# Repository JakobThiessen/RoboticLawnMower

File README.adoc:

= RoboticLawnMower
:TOC:

== Projektbeschreibung
Rasenmähroboter in Eigenbau

== Konzept

image::docs/Konzept_1.drawio.svg[static, 600]

== Projektübersicht

== Hardware
image::Hardware/KiCad/RoboticLawnMower/3D_TOP.png[static, 600]

image::Hardware/KiCad/RoboticLawnMower/3D_BOT.png[static, 600]

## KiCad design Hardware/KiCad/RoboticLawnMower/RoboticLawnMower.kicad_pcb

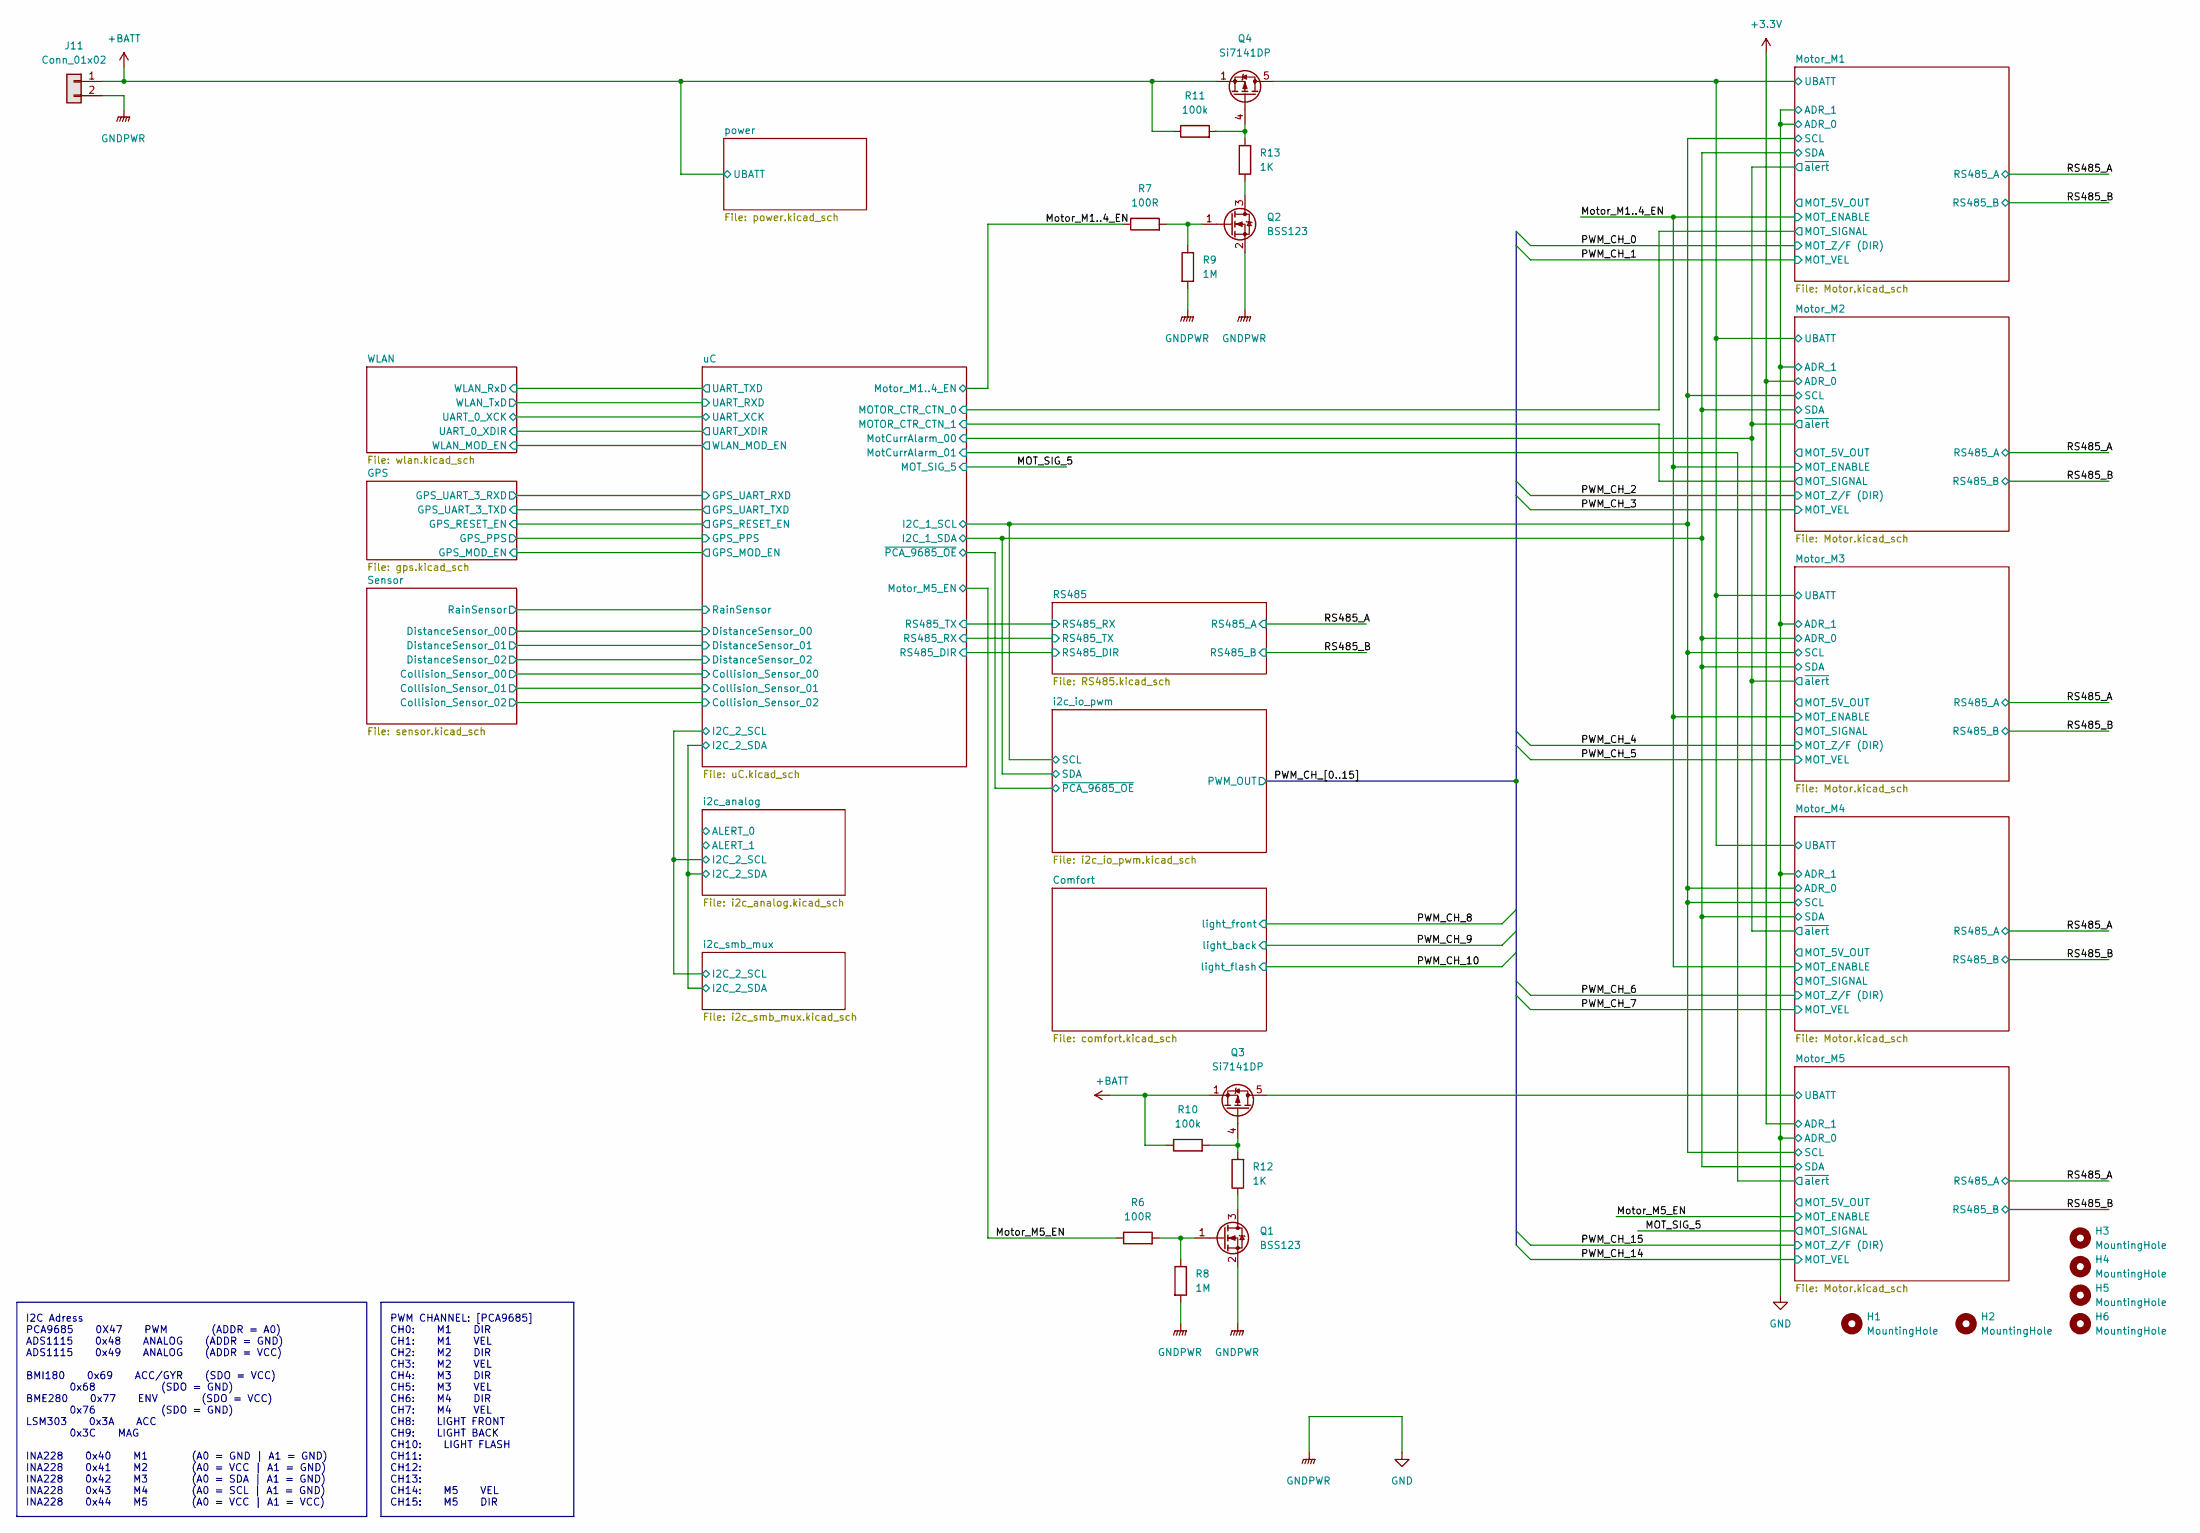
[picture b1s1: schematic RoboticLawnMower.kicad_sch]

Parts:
H1, H2, H3, H4, H5, H6: MountingHole; MountingHole_3.2mm_M3
J11: Conn_01x02; PhoenixContact_MCV_1,5_2-GF-3.81_1x02_P3.81mm_Vertical_Thre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
Q1, Q2: BSS123; SOT-23
Q3, Q4: Si7141DP; PowerPAK_SO-8_Single
R6, R7: 100R; R_0603_1608Metric
R8, R9: 1M; R_0603_1608Metric
R10, R11: 100k; R_0603_1608Metric
R12, R13: 1K; R_0603_1608Metric

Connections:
+BATT: J11.1, Q3.1 (S), Q3.2 (S), Q3.3 (S), Q4.1 (S), Q4.2 (S), Q4.3 (S), R10.1, R11.1; also elsewhere on the board
/Motor_M1..4_EN: R7.1; also elsewhere on the board
/Motor_M1/UBATT: Q4.5 (D); also elsewhere on the board
/Motor_M5/UBATT: Q3.5 (D); also elsewhere on the board
/Motor_M5_EN: R6.1; also elsewhere on the board
GND: J11.2, Q1.2 (S), Q2.2 (S), R8.2, R9.2; also elsewhere on the board
unnamed: Q1.3 (D), R12.1
unnamed: Q1.1 (G), R6.2, R8.1
unnamed: Q2.3 (D), R13.1
unnamed: Q2.1 (G), R7.2, R9.1
unnamed: Q3.4 (G), R10.2, R12.2
unnamed: Q4.4 (G), R11.2, R13.2

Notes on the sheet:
PWM CHANNEL: [PCA9685] CH0: M1 DIR CH1: M1 VEL CH2: M2 DIR CH3: M2 VEL CH4: M3 DIR CH5: M3 VEL CH6: M4 DIR CH7: M4 VEL CH8: LIGHT FRONT CH9: LIGHT BACK CH10: LIGHT FLASH CH11: CH12: CH13: CH14: M5 VEL CH15: M5 DIR
I2C Adress PCA9685 0X47 PWM (ADDR = A0) ADS1115 0x48 ANALOG (ADDR = GND) ADS1115 0x49 ANALOG (ADDR = VCC) BMI180 0x69 ACC/GYR (SDO = VCC) 0x68 (SDO = GND) BME280 0x77 ENV (SDO = VCC) 0x76 (SDO = GND) LSM303 0x3A ACC 0x3C MAG INA228 0x40 M1 (A0 = GND | A1 = GND) INA228 0x41 M2 (A0 = VCC | A1 = GND) 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

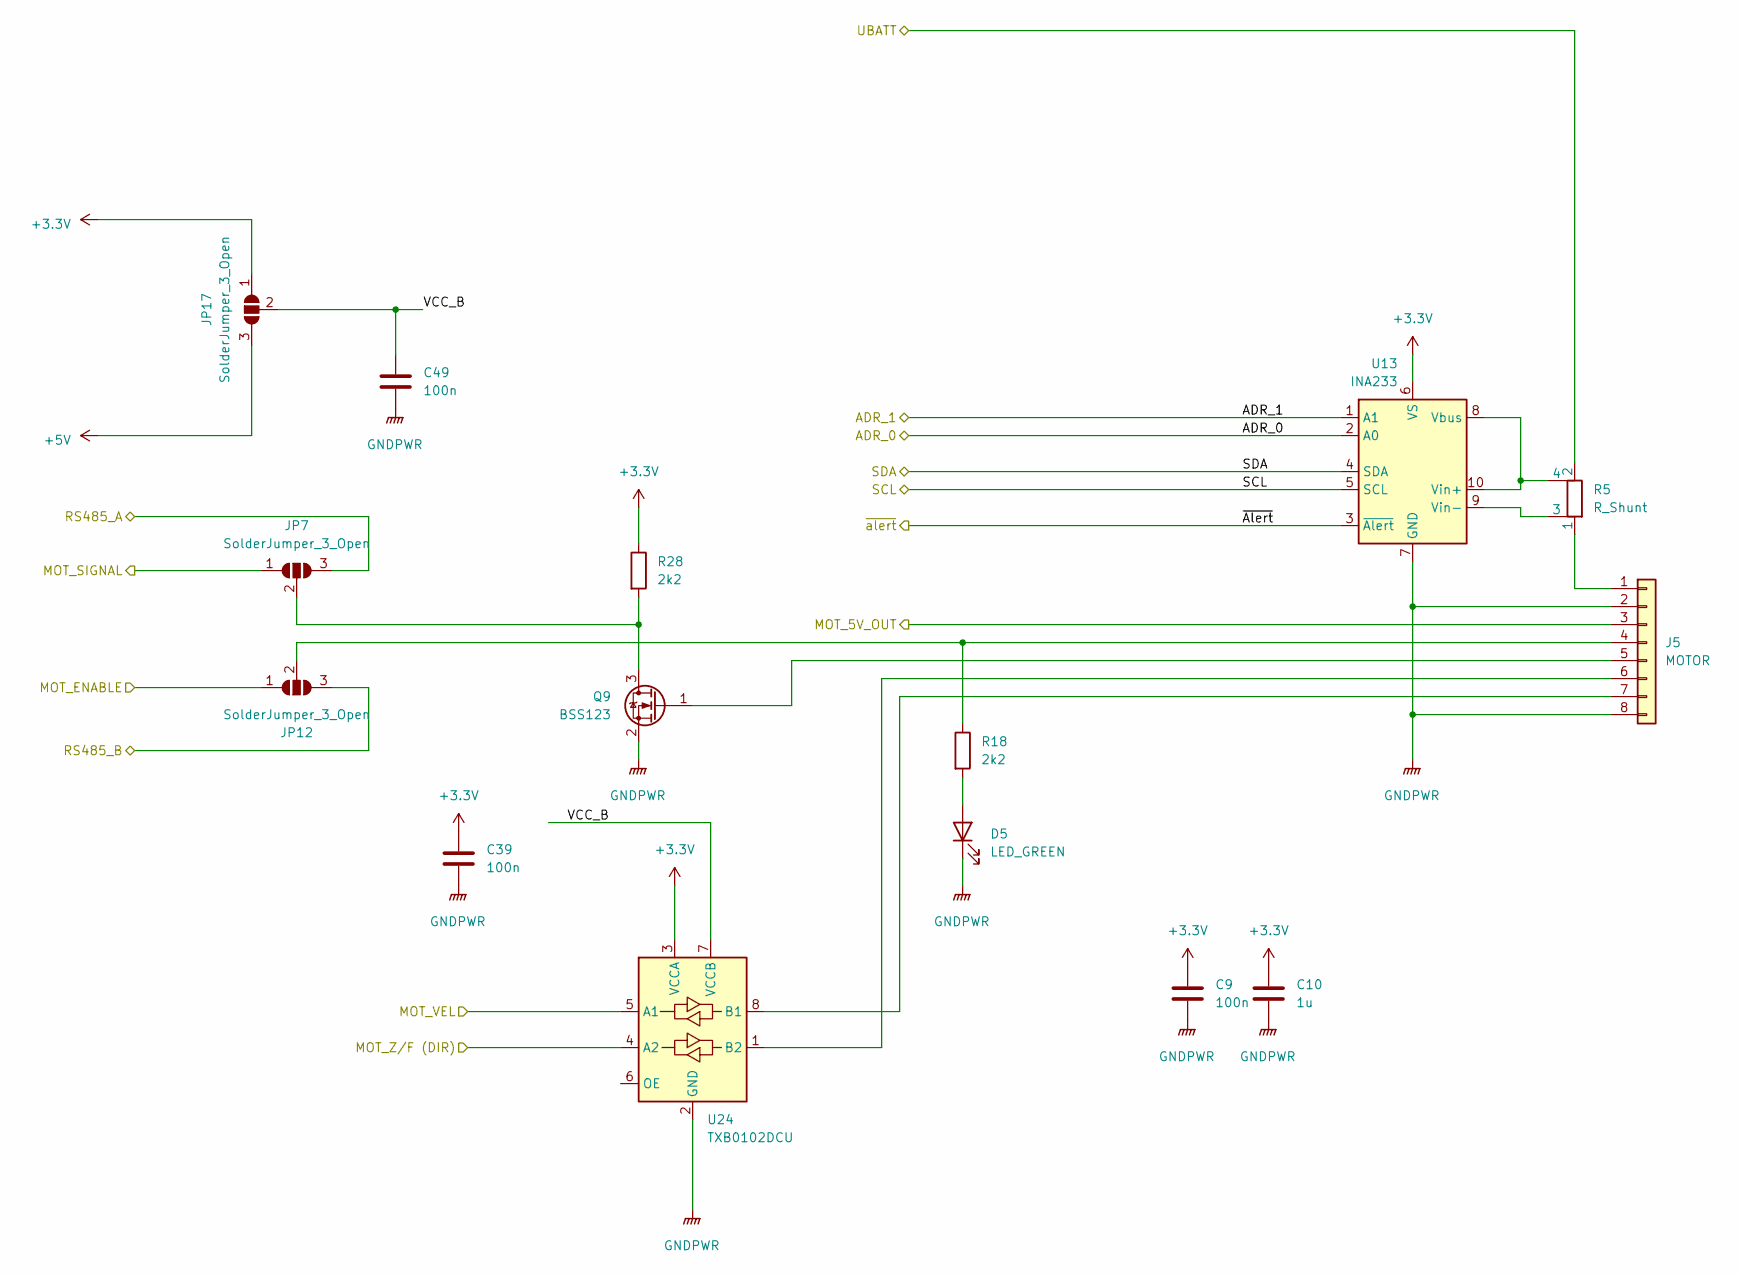
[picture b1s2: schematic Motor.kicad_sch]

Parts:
C9, C39, C49: 100n; C_0603_1608Metric
C10: 1u; C_0603_1608Metric
D5: LED_GREEN; LED_0603_1608Metric
J5: MOTOR; JST_XA_B08B-XASK-1_1x08_P2.50mm_Vertical
JP7, JP12, JP17: SolderJumper_3_Open; SolderJumper-3_P1.3mm_Open_RoundedPad1.0x1.5mm
Q9: BSS123; SOT-23
R5: R_Shunt; Y08500R10000F9R
R18, R28: 2k2; R_0603_1608Metric
U13: INA233; VSSOP-10_3x3mm_P0.5mm
U24: TXB0102DCU; VSSOP-8_2.4x2.1mm_P0.5mm

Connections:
+3.3V: C9.1, C10.1, C39.1, JP17.1 (A), R28.1, U13.1 (A1), U13.6 (VS), U24.3 (VCCA); also elsewhere on the board
+5V: JP17.3 (B); also elsewhere on the board
/MOT_SIG_5: JP7.1 (A); also elsewhere on the board
/Motor_M1/SCL: U13.5 (SCL); also elsewhere on the board
/Motor_M1/SDA: U13.4 (SDA); also elsewhere on the board
/Motor_M5/MOT_5V_OUT: J5.3
/Motor_M5/UBATT: R5.2; also elsewhere on the board
/Motor_M5/VCC_B: C49.1, JP17.2 (C), U24.7 (VCCB)
/Motor_M5/~Alert: U13.3 (~Alert); also elsewhere on the board
/Motor_M5_EN: JP12.1 (A); also elsewhere on the board
/PWM_CH_14: U24.5 (A1); also elsewhere on the board
/PWM_CH_15: U24.4 (A2); also elsewhere on the board
/RS485_A: JP7.3 (B); also elsewhere on the board
/RS485_B: JP12.3 (B); also elsewhere on the board
GND: C9.2, C10.2, C39.2, C49.2, D5.1 (K), J5.2, J5.8, Q9.2 (S), U13.2 (A0), U13.7 (GND), U24.2 (GND); also elsewhere on the board
unnamed: D5.2 (A), R18.2
unnamed: J5.1, R5.1
unnamed: J5.4, JP12.2 (C), R18.1
unnamed: J5.6, U24.1 (B2)
unnamed: J5.7, U24.8 (B1)
unnamed: R5.4, U13.8 (Vbus), U13.10 (Vin+)
unnamed: R5.3, U13.9 (Vin-)

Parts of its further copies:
C1, C3, C5, C7, C35, C36, C37, C38, C45, C46, C47, C48: 100n; C_0603_1608Metric
C2, C4, C6, C8: 1u; C_0603_1608Metric
D1, D2, D3, D4: LED_GREEN; LED_0603_1608Metric
J1, J2, J3, J4: MOTOR; JST_XA_B08B-XASK-1_1x08_P2.50mm_Vertical
JP3, JP4, JP5, JP6, JP8, JP9, JP10, JP11, JP13, JP14, JP15, JP16: SolderJumper_3_Open; SolderJumper-3_P1.3mm_Open_RoundedPad1.0x1.5mm
Q10, Q11, Q12, Q13: BSS123; SOT-23
R1, R2, R3, R4: R_Shunt; Y08500R10000F9R
R14, R15, R16, R17, R29, R30, R31, R32: 2k2; R_0603_1608Metric
U1, U10, U11, U12: INA233; VSSOP-10_3x3mm_P0.5mm
U20, U21, U22, U23: TXB0102DCU; VSSOP-8_2.4x2.1mm_P0.5mm

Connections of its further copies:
+3.3V: C1.1, C2.1, C3.1, C4.1, C5.1, C6.1, C7.1, C8.1, C35.1, C36.1, C37.1, C38.1, JP13.1 (A), JP14.1 (A), JP15.1 (A), JP16.1 (A), R29.1, R30.1, R31.1, R32.1, U1.6 (VS), U10.2 (A0), U10.6 (VS), U11.6 (VS), U12.6 (VS), U20.3 (VCCA), U21.3 (VCCA), U22.3 (VCCA), U23.3 (VCCA); also elsewhere on the board
+5V: JP13.3 (B), JP14.3 (B), JP15.3 (B), JP16.3 (B); also elsewhere on the board
/Motor_M1..4_EN: JP8.1 (A), JP9.1 (A), JP10.1 (A), JP11.1 (A); also elsewhere on the board
/Motor_M1/MOT_5V_OUT: J1.3
/Motor_M1/MOT_SIGNAL: JP3.1 (A); also elsewhere on the board
/Motor_M1/SCL: U1.5 (SCL), U10.5 (SCL), U11.5 (SCL), U12.2 (A0), U12.5 (SCL); also elsewhere on the board
/Motor_M1/SDA: U1.4 (SDA), U10.4 (SDA), U11.2 (A0), U11.4 (SDA), U12.4 (SDA); also elsewhere on the board
/Motor_M1/UBATT: R1.2, R2.2, R3.2, R4.2; also elsewhere on the board
/Motor_M1/VCC_B: C45.1, JP13.2 (C), U20.7 (VCCB)
/Motor_M1/~Alert: U1.3 (~Alert), U10.3 (~Alert), U11.3 (~Alert), U12.3 (~Alert); also elsewhere on the board
/Motor_M2/MOT_5V_OUT: J2.3
/Motor_M2/MOT_SIGNAL: JP4.1 (A); also elsewhere on the board
/Motor_M2/VCC_B: C46.1, JP14.2 (C), U21.7 (VCCB)
/Motor_M3/MOT_5V_OUT: J3.3
/Motor_M3/MOT_SIGNAL: JP5.1 (A)
/Motor_M3/VCC_B: C47.1, JP15.2 (C), U22.7 (VCCB)
/Motor_M4/MOT_5V_OUT: J4.3
/Motor_M4/MOT_SIGNAL: JP6.1 (A)
/Motor_M4/VCC_B: C48.1, JP16.2 (C), U23.7 (VCCB)
/PWM_CH_0: U20.4 (A2); also elsewhere on the board
/PWM_CH_1: U20.5 (A1); also elsewhere on the board
/PWM_CH_2: U21.4 (A2); also elsewhere on the board
/PWM_CH_3: U21.5 (A1); also elsewhere on the board
/PWM_CH_4: U22.4 (A2); also elsewhere on the board
/PWM_CH_5: U22.5 (A1); also elsewhere on the board
/PWM_CH_6: U23.4 (A2); also elsewhere on the board
/PWM_CH_7: U23.5 (A1); also elsewhere on the board
/RS485_A: JP3.3 (B), JP4.3 (B), JP5.3 (B), JP6.3 (B); also elsewhere on the board
/RS485_B: JP8.3 (B), JP9.3 (B), JP10.3 (B), JP11.3 (B); also elsewhere on the board
GND: C1.2, C2.2, C3.2, C4.2, C5.2, C6.2, C7.2, C8.2, C35.2, C36.2, C37.2, C38.2, C45.2, C46.2, C47.2, C48.2, D1.1 (K), D2.1 (K), D3.1 (K), D4.1 (K), J1.2, J1.8, J2.2, J2.8, J3.2, J3.8, J4.2, J4.8, Q10.2 (S), Q11.2 (S), Q12.2 (S), Q13.2 (S), U1.1 (A1), U1.2 (A0), U1.7 (GND), U10.1 (A1), U10.7 (GND), U11.1 (A1), U11.7 (GND), U12.1 (A1), U12.7 (GND), U20.2 (GND), U21.2 (GND), U22.2 (GND), U23.2 (GND); also elsewhere on the board
unnamed: D1.2 (A), R14.2
unnamed: D2.2 (A), R15.2
unnamed: D3.2 (A), R16.2
unnamed: D4.2 (A), R17.2
unnamed: J1.1, R1.1
unnamed: J1.4, JP8.2 (C), R14.1
unnamed: J1.6, U20.1 (B2)
unnamed: J1.7, U20.8 (B1)
unnamed: J2.1, R2.1
unnamed: J2.4, JP9.2 (C), R15.1
unnamed: J2.5, Q10.1 (G)
unnamed: J2.6, U21.1 (B2)
unnamed: J2.7, U21.8 (B1)
unnamed: J3.1, R3.1
unnamed: J3.4, JP10.2 (C), R16.1
unnamed: J3.5, Q11.1 (G)
unnamed: J3.6, U22.1 (B2)
unnamed: J3.7, U22.8 (B1)
unnamed: J4.1, R4.1
unnamed: J4.4, JP11.2 (C), R17.1
unnamed: J4.5, Q12.1 (G)
unnamed: J4.6, U23.1 (B2)
unnamed: J4.7, U23.8 (B1)
unnamed: JP4.2 (C), Q10.3 (D), R29.2
unnamed: JP5.2 (C), Q11.3 (D), R30.2
unnamed: JP6.2 (C), Q12.3 (D), R31.2
unnamed: R1.4, U1.8 (Vbus), U1.10 (Vin+)
unnamed: R1.3, U1.9 (Vin-)
unnamed: R2.4, U10.8 (Vbus), U10.10 (Vin+)
unnamed: R2.3, U10.9 (Vin-)
unnamed: R3.4, U11.8 (Vbus), U11.10 (Vin+)
unnamed: R3.3, U11.9 (Vin-)
unnamed: R4.4, U12.8 (Vbus), U12.10 (Vin+)
unnamed: R4.3, U12.9 (Vin-)

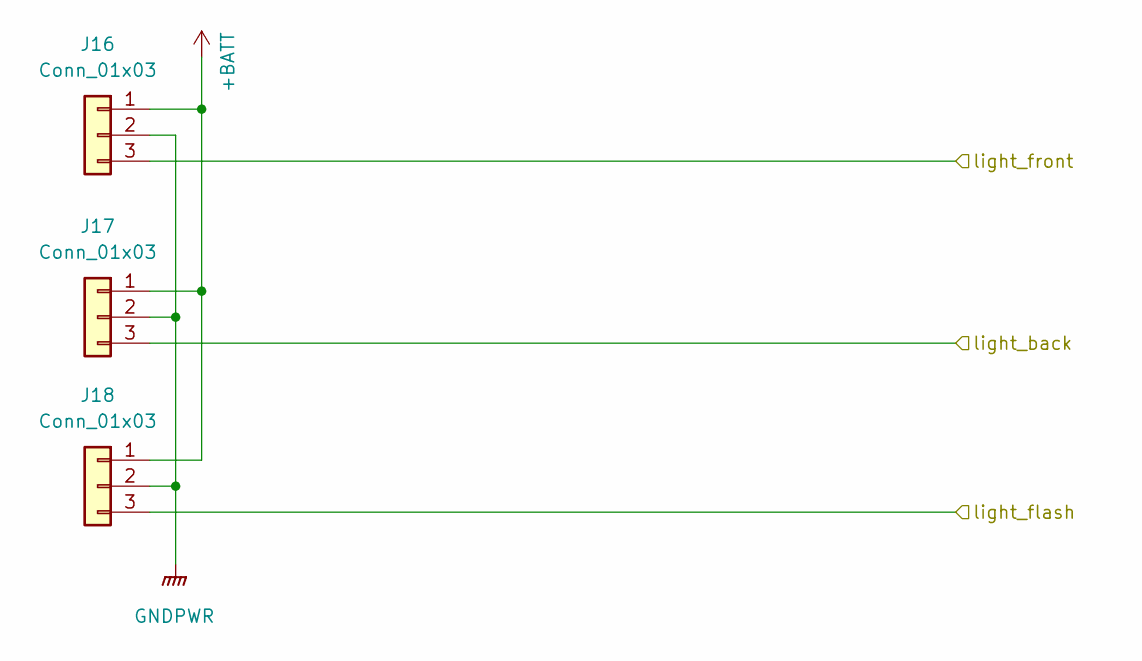
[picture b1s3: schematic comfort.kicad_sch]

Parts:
J16, J17, J18: Conn_01x03; JST_XA_B03B-XASK-1_1x03_P2.50mm_Vertical

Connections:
+BATT: J16.1, J17.1, J18.1; also elsewhere on the board
/PWM_CH_8: J16.3; also elsewhere on the board
/PWM_CH_9: J17.3; also elsewhere on the board
/PWM_CH_10: J18.3; also elsewhere on the board
GND: J16.2, J17.2, J18.2; also elsewhere on the board

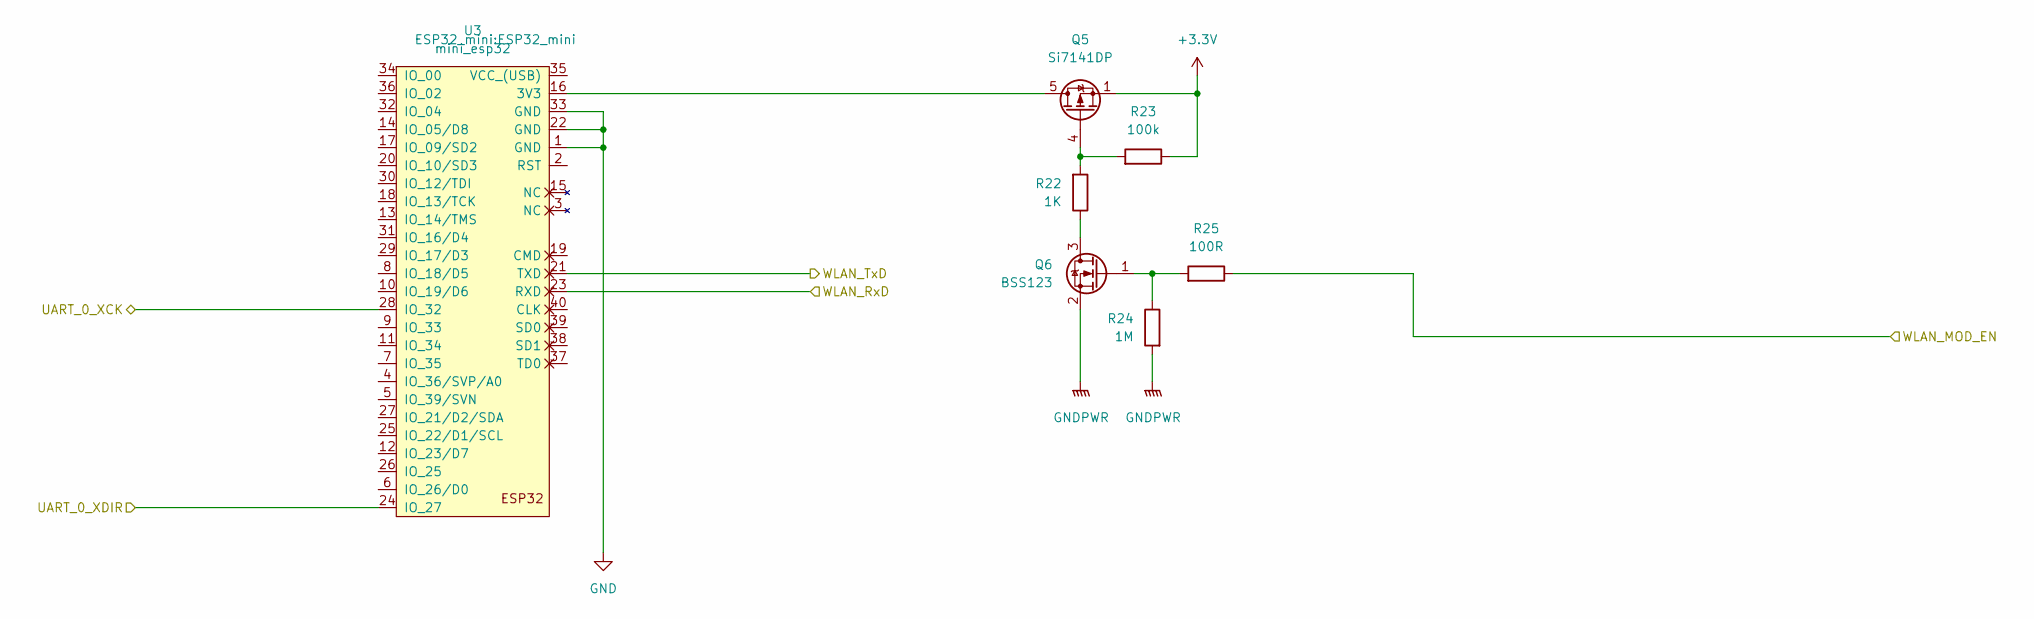
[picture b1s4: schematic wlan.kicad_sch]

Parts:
Q5: Si7141DP; PowerPAK_SO-8_Single
Q6: BSS123; SOT-23
R22: 1K; R_0603_1608Metric
R23: 100k; R_0603_1608Metric
R24: 1M; R_0603_1608Metric
R25: 100R; R_0603_1608Metric
U3: mini_esp32; ESP32_mini

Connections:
+3.3V: Q5.1 (S), Q5.2 (S), Q5.3 (S), R23.1; also elsewhere on the board
/WLAN/UART_0_XCK: U3.28 (IO_32); also elsewhere on the board
/WLAN/UART_0_XDIR: U3.24 (IO_27); also elsewhere on the board
/WLAN/WLAN_MOD_EN: R25.1; also elsewhere on the board
/uC/USART_2_RX: U3.21 (TXD); also elsewhere on the board
/uC/USART_2_TX: U3.23 (RXD); also elsewhere on the board
GND: Q6.2 (S), R24.2, U3.1 (GND), U3.22 (GND), U3.33 (GND); also elsewhere on the board
unnamed: Q5.5 (D), U3.16 (3V3)
unnamed: Q5.4 (G), R22.2, R23.2
unnamed: Q6.3 (D), R22.1
unnamed: Q6.1 (G), R24.1, R25.2

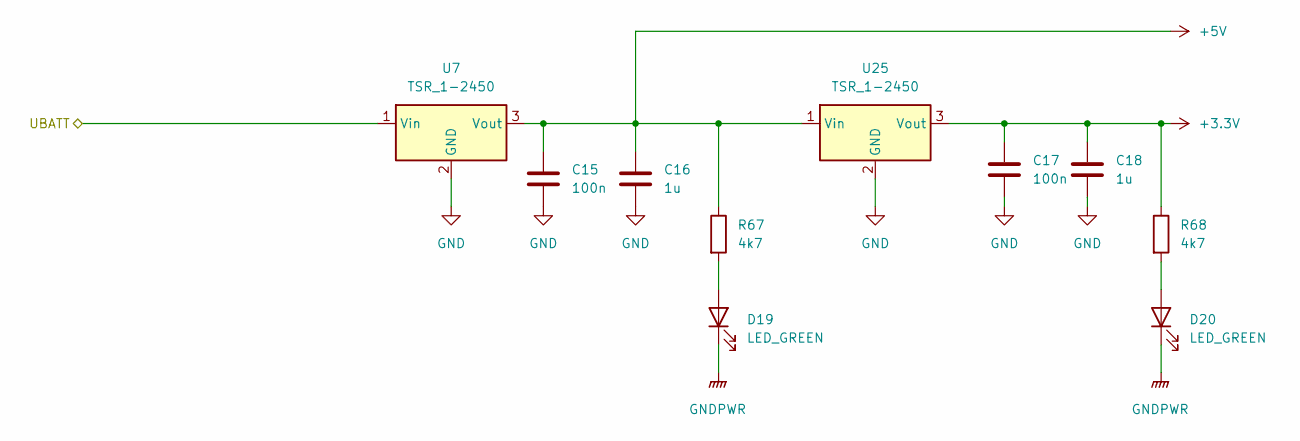
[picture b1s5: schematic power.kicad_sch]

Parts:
C15, C17: 100n; C_0603_1608Metric
C16, C18: 1u; C_0603_1608Metric
D19, D20: LED_GREEN; LED_0603_1608Metric
R67, R68: 4k7; R_0603_1608Metric
U7, U25: TSR_1-2450; Converter_DCDC_TRACO_TSR-1_THT

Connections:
+3.3V: C17.1, C18.1, R68.1, U25.3 (Vout); also elsewhere on the board
+5V: C15.1, C16.1, R67.1, U7.3 (Vout), U25.1 (Vin); also elsewhere on the board
+BATT: U7.1 (Vin); also elsewhere on the board
GND: C15.2, C16.2, C17.2, C18.2, D19.1 (K), D20.1 (K), U7.2 (GND), U25.2 (GND); also elsewhere on the board
unnamed: D19.2 (A), R67.2
unnamed: D20.2 (A), R68.2

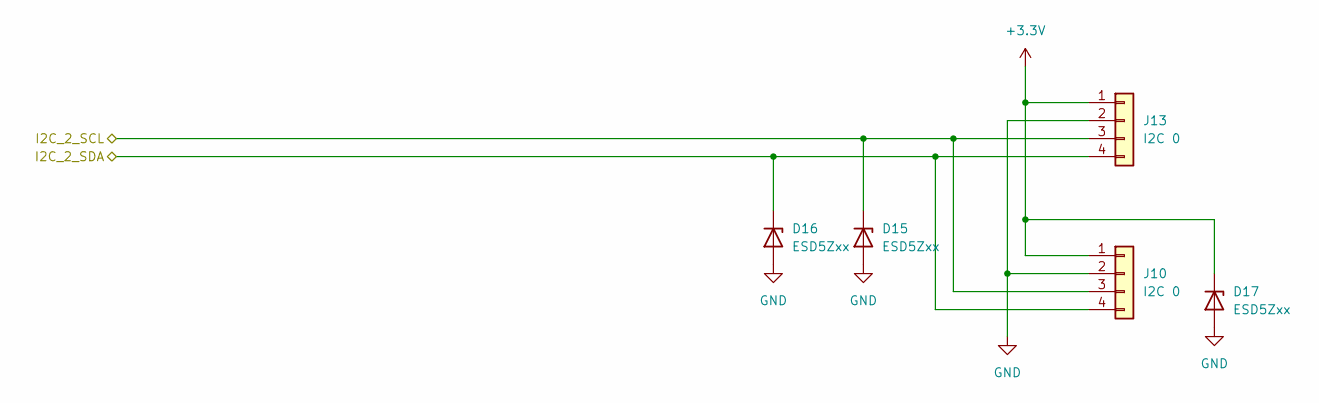
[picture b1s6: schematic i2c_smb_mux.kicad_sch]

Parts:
D15, D16, D17: ESD5Zxx; D_SOD-523
J10, J13: I2C 0; JST_XA_B04B-XASK-1_1x04_P2.50mm_Vertical

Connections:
+3.3V: D17.1 (K), J10.1, J13.1; also elsewhere on the board
/i2c_analog/I2C_2_SCL: D15.1 (K), J10.3, J13.3; also elsewhere on the board
/i2c_analog/I2C_2_SDA: D16.1 (K), J10.4, J13.4; also elsewhere on the board
GND: D15.2 (A), D16.2 (A), D17.2 (A), J10.2, J13.2; also elsewhere on the board

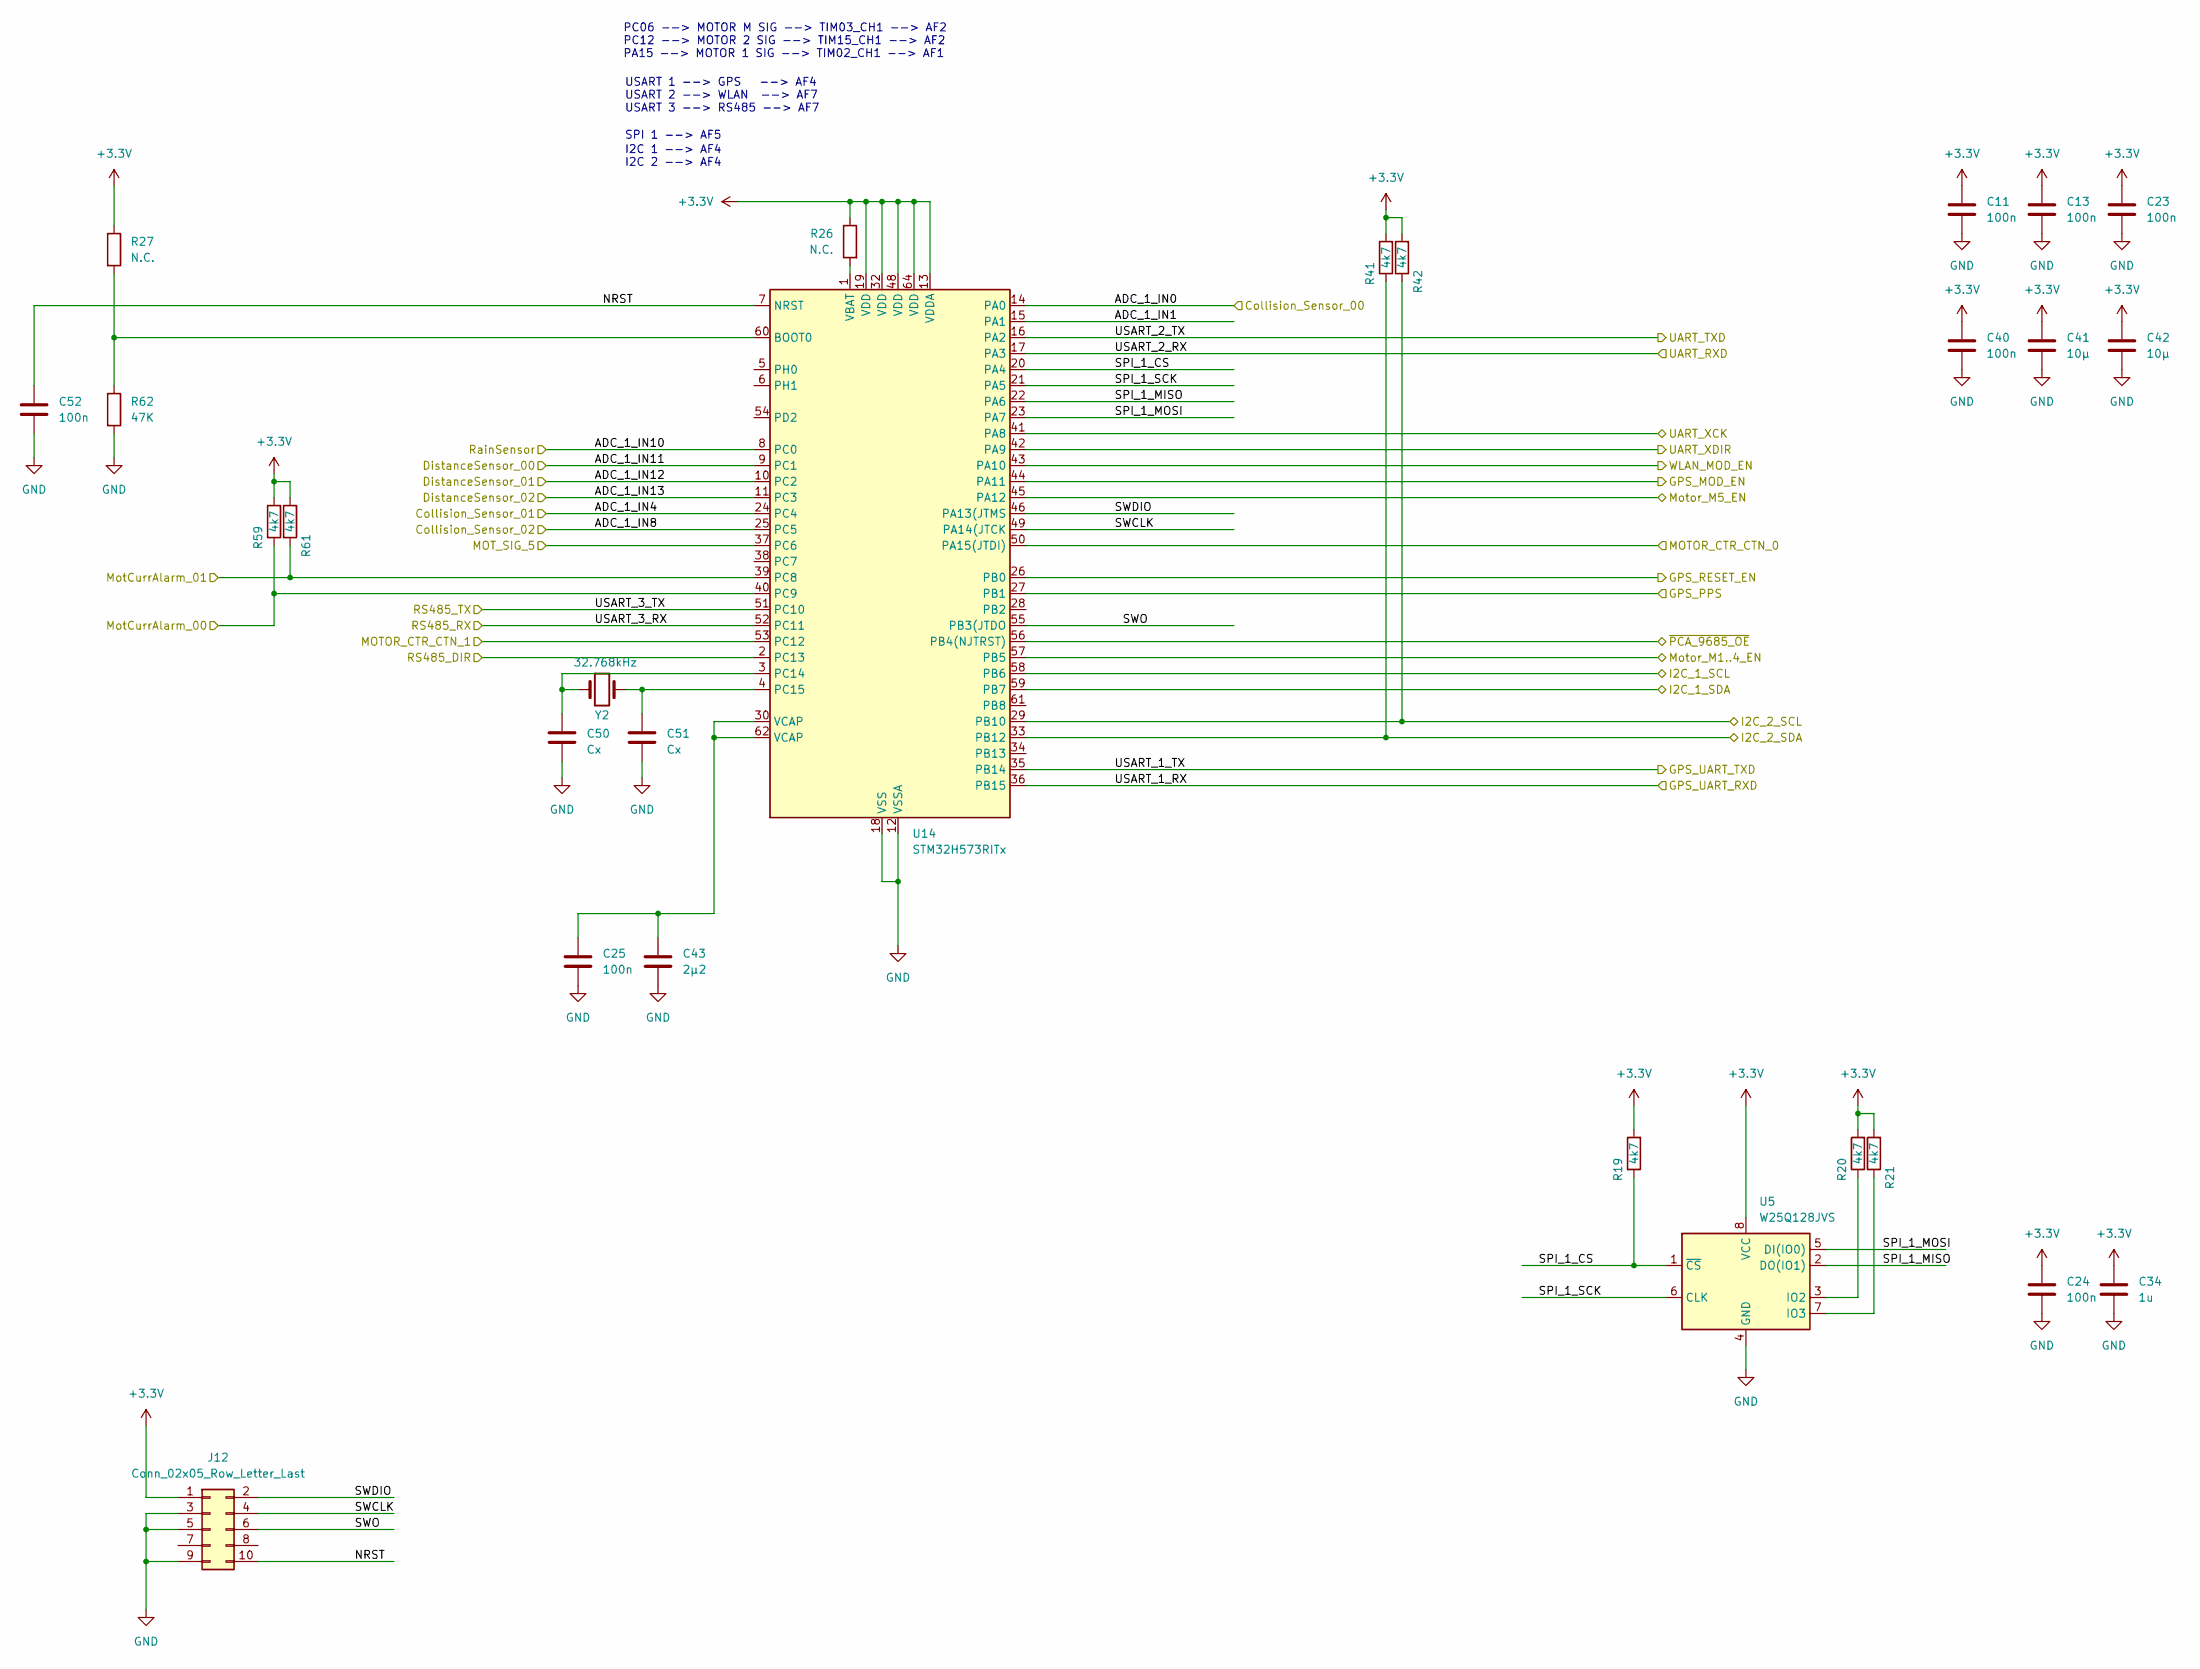
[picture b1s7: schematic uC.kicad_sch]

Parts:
C11, C13, C23, C24, C25, C40, C52: 100n; C_0603_1608Metric
C34: 1u; C_0603_1608Metric
C41, C42: 10µ; C_0603_1608Metric
C43: 2µ2; C_0603_1608Metric
C50, C51: Cx; C_0603_1608Metric
J12: Conn_02x05_Row_Letter_Last; PinHeader_2x05_P1.27mm_Vertical_SMD
R19, R20, R21, R41, R42, R59, R61: 4k7; R_0603_1608Metric
R26, R27: N.C.; R_0603_1608Metric
R62: 47K; R_0603_1608Metric
U5: W25Q128JVS; SOIC-8_5.23x5.23mm_P1.27mm
U14: STM32H573RITx; LQFP-64_10x10mm_P0.5mm
Y2: 32.768kHz; Crystal_SMD_3215-2Pin_3.2x1.5mm

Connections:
+3.3V: C11.1, C13.1, C23.1, C24.1, C34.1, C40.1, C41.1, C42.1, J12.1, R19.2, R20.2, R21.2, R26.1, R27.1, R41.2, R42.2, R59.2, R61.2, U5.8 (VCC), U14.13 (VDDA), U14.19 (VDD), U14.32 (VDD), U14.48 (VDD), U14.64 (VDD); also elsewhere on the board
/GPS/GPS_MOD_EN: U14.44 (PA11); also elsewhere on the board
/GPS/GPS_PPS: U14.27 (PB1); also elsewhere on the board
/GPS/GPS_RESET_EN: U14.26 (PB0); also elsewhere on the board
/MOT_SIG_5: U14.37 (PC6); also elsewhere on the board
/Motor_M1..4_EN: U14.57 (PB5); also elsewhere on the board
/Motor_M1/MOT_SIGNAL: U14.50 (PA15(JTDI)); also elsewhere on the board
/Motor_M1/SCL: U14.58 (PB6); also elsewhere on the board
/Motor_M1/SDA: U14.59 (PB7); also elsewhere on the board
/Motor_M1/~Alert: R59.1, U14.40 (PC9); also elsewhere on the board
/Motor_M2/MOT_SIGNAL: U14.53 (PC12); also elsewhere on the board
/Motor_M5/~Alert: R61.1, U14.39 (PC8); also elsewhere on the board
/Motor_M5_EN: U14.45 (PA12); also elsewhere on the board
/RS485/RS485_DIR: U14.2 (PC13); also elsewhere on the board
/Sensor/DistanceSensor_00: U14.9 (PC1); also elsewhere on the board
/Sensor/DistanceSensor_01: U14.10 (PC2); also elsewhere on the board
/Sensor/DistanceSensor_02: U14.11 (PC3); also elsewhere on the board
/Sensor/RainSensor: U14.8 (PC0); also elsewhere on the board
/WLAN/UART_0_XCK: U14.41 (PA8); also elsewhere on the board
/WLAN/UART_0_XDIR: U14.42 (PA9); also elsewhere on the board
/WLAN/WLAN_MOD_EN: U14.43 (PA10); also elsewhere on the board
/i2c_analog/I2C_2_SCL: R42.1, U14.29 (PB10); also elsewhere on the board
/i2c_analog/I2C_2_SDA: R41.1, U14.33 (PB12); also elsewhere on the board
/i2c_io_pwm/~PCA_9685_OE: U14.56 (PB4(NJTRST)); also elsewhere on the board
/uC/ADC_1_IN0: U14.14 (PA0); also elsewhere on the board
/uC/ADC_1_IN1: U14.15 (PA1)
/uC/ADC_1_IN4: U14.24 (PC4); also elsewhere on the board
/uC/ADC_1_IN8: U14.25 (PC5); also elsewhere on the board
/uC/NRST: C52.1, J12.10, U14.7 (NRST)
/uC/SPI_1_CS: R19.1, U5.1 (~CS), U14.20 (PA4)
/uC/SPI_1_MISO: U5.2 (DO(IO1)), U14.22 (PA6)
/uC/SPI_1_MOSI: U5.5 (DI(IO0)), U14.23 (PA7)
/uC/SPI_1_SCK: U5.6 (CLK), U14.21 (PA5)
/uC/SWCLK: J12.4, U14.49 (PA14(JTCK)
/uC/SWDIO: J12.2, U14.46 (PA13(JTMS)
/uC/SWO: J12.6, U14.55 (PB3(JTDO)
/uC/USART_1_RX: U14.36 (PB15); also elsewhere on the board
/uC/USART_1_TX: U14.35 (PB14); also elsewhere on the board
/uC/USART_2_RX: U14.17 (PA3); also elsewhere on the board
/uC/USART_2_TX: U14.16 (PA2); also elsewhere on the board
/uC/USART_3_RX: U14.52 (PC11); also elsewhere on the board
/uC/USART_3_TX: U14.51 (PC10); also elsewhere on the board
GND: C11.2, C13.2, C23.2, C24.2, C25.2, C34.2, C40.2, C41.2, C42.2, C43.2, C50.2, C51.2, C52.2, J12.3, J12.5, J12.9, R62.2, U5.4 (GND), U14.12 (VSSA), U14.18 (VSS), U14.31 (VSS), U14.47 (VSS), U14.63 (VSS); also elsewhere on the board
unnamed: C25.1, C43.1, U14.30 (VCAP), U14.62 (VCAP)
unnamed: R20.1, U5.3 (IO2)
unnamed: R21.1, U5.7 (IO3)
unnamed: R27.2, R62.1, U14.60 (BOOT0)
unnamed: C50.1, U14.3 (PC14), Y2.1
unnamed: C51.1, U14.4 (PC15), Y2.2
unnamed: R26.2, U14.1 (VBAT)

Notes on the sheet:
PC06 --> MOTOR M SIG --> TIM03_CH1 --> AF2 PC12 --> MOTOR 2 SIG --> TIM15_CH1 --> AF2 PA15 --> MOTOR 1 SIG --> TIM02_CH1 --> AF1
USART 1 --> GPS --> AF4 USART 2 --> WLAN --> AF7 USART 3 --> RS485 --> AF7
I2C 2 --> AF4
SPI 1 --> AF5
I2C 1 --> AF4

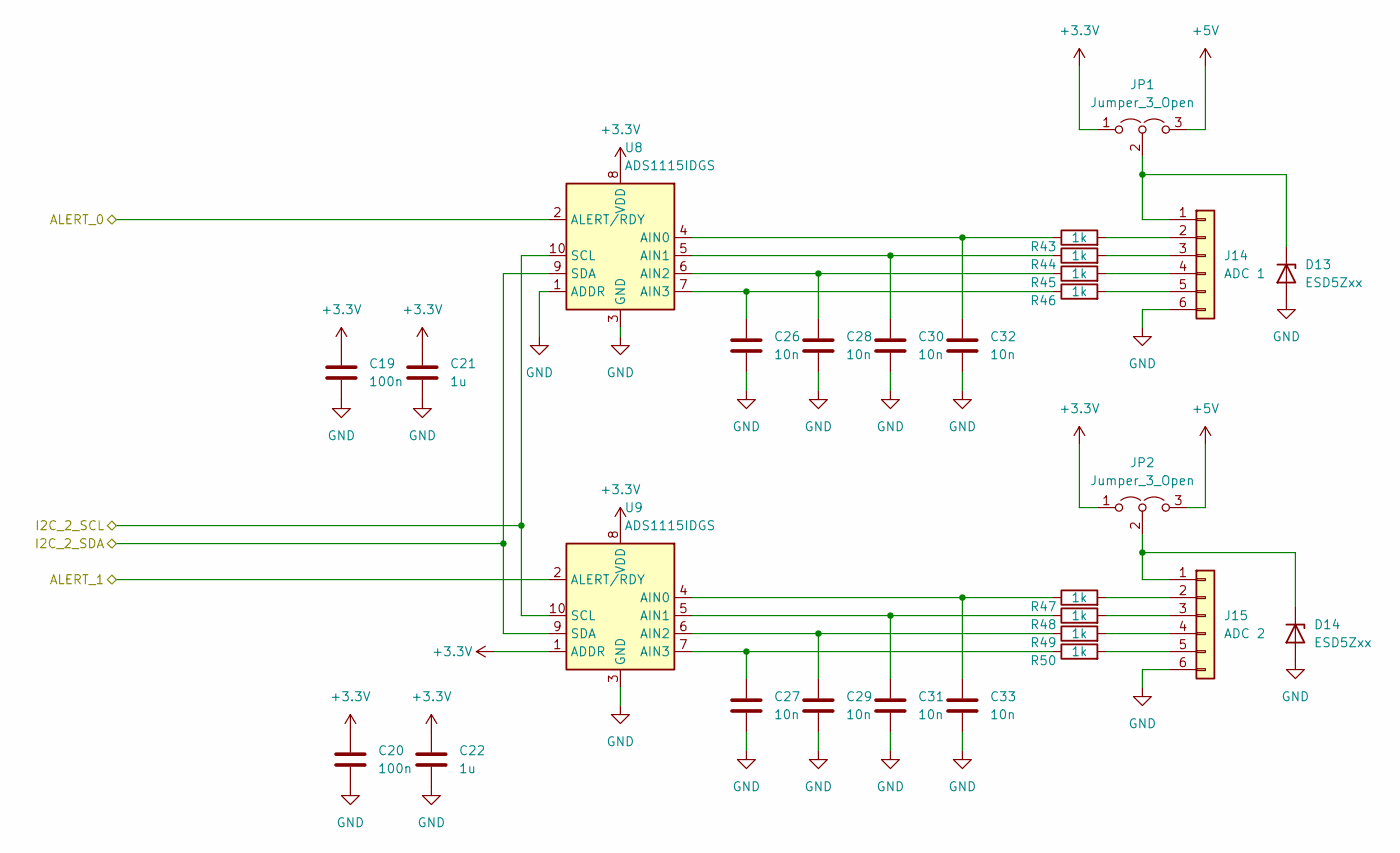
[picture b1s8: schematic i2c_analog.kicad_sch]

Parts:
C19, C20: 100n; C_0603_1608Metric
C21, C22: 1u; C_0603_1608Metric
C26, C27, C28, C29, C30, C31, C32, C33: 10n; C_0603_1608Metric
D13, D14: ESD5Zxx; D_SOD-523
J14: ADC 1; JST_XA_B06B-XASK-1_1x06_P2.50mm_Vertical
J15: ADC 2; JST_XA_B06B-XASK-1_1x06_P2.50mm_Vertical
JP1, JP2: Jumper_3_Open; SolderJumper-3_P1.3mm_Bridged12_RoundedPad1.0x1.5mm
R43, R44, R45, R46, R47, R48, R49, R50: 1k; R_0603_1608Metric
U8, U9: ADS1115IDGS; TSSOP-10_3x3mm_P0.5mm

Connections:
+3.3V: C19.1, C20.1, C21.1, C22.1, JP1.1 (A), JP2.1 (A), U8.8 (VDD), U9.1 (ADDR), U9.8 (VDD); also elsewhere on the board
+5V: JP1.3 (B), JP2.3 (B); also elsewhere on the board
/i2c_analog/ALERT_0: U8.2 (ALERT/RDY)
/i2c_analog/ALERT_1: U9.2 (ALERT/RDY)
/i2c_analog/I2C_2_SCL: U8.10 (SCL), U9.10 (SCL); also elsewhere on the board
/i2c_analog/I2C_2_SDA: U8.9 (SDA), U9.9 (SDA); also elsewhere on the board
GND: C19.2, C20.2, C21.2, C22.2, C26.2, C27.2, C28.2, C29.2, C30.2, C31.2, C32.2, C33.2, D13.2 (A), D14.2 (A), J14.6, J15.6, U8.1 (ADDR), U8.3 (GND), U9.3 (GND); also elsewhere on the board
unnamed: D13.1 (K), J14.1, JP1.2 (C)
unnamed: D14.1 (K), J15.1, JP2.2 (C)
unnamed: J14.2, R43.2
unnamed: J14.3, R44.2
unnamed: J14.4, R45.2
unnamed: J14.5, R46.2
unnamed: J15.2, R47.2
unnamed: J15.3, R48.2
unnamed: J15.4, R49.2
unnamed: J15.5, R50.2
unnamed: C32.1, R43.1, U8.4 (AIN0)
unnamed: C30.1, R44.1, U8.5 (AIN1)
unnamed: C28.1, R45.1, U8.6 (AIN2)
unnamed: C26.1, R46.1, U8.7 (AIN3)
unnamed: C33.1, R47.1, U9.4 (AIN0)
unnamed: C31.1, R48.1, U9.5 (AIN1)
unnamed: C29.1, R49.1, U9.6 (AIN2)
unnamed: C27.1, R50.1, U9.7 (AIN3)

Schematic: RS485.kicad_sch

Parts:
C53: 100n; C_0603_1608Metric
C54: 1u; C_0603_1608Metric
R69: 120; R_1206_3216Metric
U2: LT1785AxS8; SOIC-8_3.9x4.9mm_P1.27mm

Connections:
+3.3V: C53.1, C54.1, U2.8 (VCC); also elsewhere on the board
/RS485/RS485_DIR: U2.2 (~RE), U2.3 (DE); also elsewhere on the board
/RS485_A: R69.1, U2.6 (A); also elsewhere on the board
/RS485_B: R69.2, U2.7 (B); also elsewhere on the board
/uC/USART_3_RX: U2.1 (RO); also elsewhere on the board
/uC/USART_3_TX: U2.4 (DI); also elsewhere on the board
GND: C53.2, C54.2, U2.5 (GND); also elsewhere on the board
